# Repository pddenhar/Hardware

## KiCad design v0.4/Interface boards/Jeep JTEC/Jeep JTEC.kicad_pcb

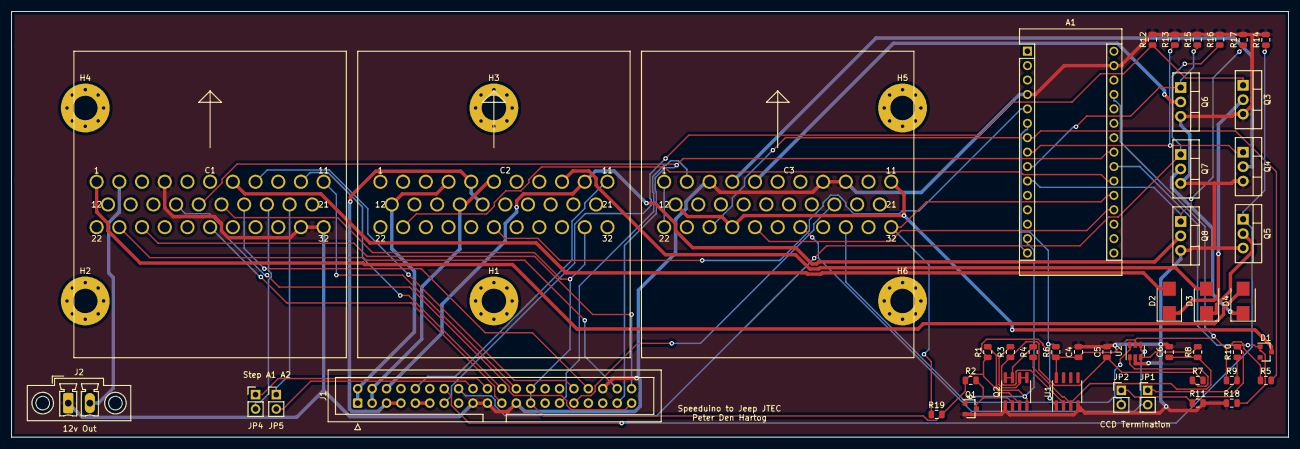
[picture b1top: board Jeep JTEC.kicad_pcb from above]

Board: 2 copper layers, 225.0 x 75.0 mm, 52 parts (0 on the bottom side), 59 nets.

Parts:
A1: Arduino_Nano_v3.x; Arduino_Nano
C1, C2, C3: Conn_01x32; mopar_32pin_pcm
C4: 0.1u; C_0805_2012Metric
C5, C6: 3.3n; C_0805_2012Metric
D1: 10V; SOT-23
D2, D3, D4: D_Schottky 200v; D_SMB
H1, H2, H3, H4, H5, H6: MountingHole; MountingHole_4.3mm_M4_Pad_Via
J1: Conn_02x20_Counter_Clockwise; IDC-Header_2x20_P2.54mm_Vertical
J2: 12v SW Output; PhoenixContact_MCV_1,5_2-GF-3.81_1x02_P3.81mm_Vertical_Thre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
JP1, JP2, JP4, JP5: NO; PinHeader_1x02_P2.54mm_Vertical
Q1: AO3400; SOT-23
Q2: IRF7317; SOIC-8_3.9x4.9mm_P1.27mm
Q3, Q4, Q5, Q6, Q7, Q8: IRF540NPBF; TO-220-3_Vertical
R1, R2, R5, R6, R12, R13, R14, R15, R16, R17, R18, R19: 10k; R_0805_2012Metric
R3, R4: 360; R_0805_2012Metric
R7, R8: 10; R_0805_2012Metric
R9, R11: 13k; R_0805_2012Metric
R10: 120; R_0805_2012Metric
U1: LM2903; SOIC-8_3.9x4.9mm_P1.27mm
U2: USBLC6-2SC6; SOT-23-6

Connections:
12V-SW: C1.2, J2.2
/CCD Decoder/CCD_RX: A1.6, A1.15, R6.2, U1.1
/CCD Decoder/CCD_SAFE+: C5.1, R3.1, R7.2, U1.2
/CCD Decoder/CCD_SAFE-: C6.1, R4.1, R8.1, U1.3
/CCD Decoder/CCD_TX: A1.14, Q1.1, Q2.4, R1.2
/CCD Decoder/NOT-gate: Q1.3, Q2.2, R2.2
AC_CLUTCH_OUT: C3.1, C3.22
ASD_12V_IN: C3.11, C3.12, C3.25, D1.3
ASD_COIL_OUT: A1.4, A1.29, C1.4, C1.31, C1.32, C3.3, C3.8, C3.9, C4.2, C5.2, C6.2, J1.17, J1.19, J1.23, J1.36, J2.1, Q1.2, Q2.1, Q3.3, Q4.3, Q5.3, Q6.3, Q7.3, Q8.3, R11.2, R12.2, R13.2, R14.2, R15.2, R16.2, R17.2, R18.1, U1.4, U2.2
BRAKE_LAMP_SWITCH: A1.7, C3.24, R5.2
CAM-IN: C1.18, J1.34
CCD+: C3.30, JP2.2, U2.6
CCD-: C3.28, JP1.2, U2.4
CLT_Sensor: A1.23, C1.16, J1.37
CRANK-IN: C1.8, J1.32
CRUISE_VAC_CONTROL: A1.8, Q4.1, R13.1
CRUISE_VAC_OUT: C3.4, Q4.2
CRUISE_VENT_CONTROL: A1.9, Q6.1, R15.1
CRUISE_VENT_OUT: C3.5, Q6.2
FAN-OUT: C3.2, J1.29
FUELPUMP-OUT: C3.19, J1.31
FUEL_LEVEL: A1.19, C3.26
GENERATOR_CONTROL: A1.10, Q8.1, R17.1
GENERATOR_GND: C2.10, J1.6, Q8.2
HC-1-OUT: C2.11, J1.10
IAT_Sensor: C1.15, J1.39
IGN-1-DRIVER: C1.7, D2.2
IGN-1-OUT: J1.13, Q3.1, R12.1
IGN-2-DRIVER: C2.9, D3.2
IGN-2-OUT: J1.14, Q5.1, R14.1
IGN-3-DRIVER: C1.1, D4.2
IGN-3-OUT: J1.16, Q7.1, R16.1
INJ-1-OUT: C2.4, C2.12, J1.1, J1.2
INJ-2-OUT: C2.6, C2.15, J1.3, J1.4
INJ-3-OUT: C2.5, C2.16, J1.5, J1.7
INJ-4-OUT: J1.9, J1.11
MAP-EXT: C1.27, J1.21
unnamed: A1.22, D1.1, R18.2
unnamed: C1.19, JP4.2
unnamed: C1.20, JP5.1
unnamed: D2.1, Q3.2
unnamed: D3.1, Q5.2
unnamed: D4.1, Q7.2
unnamed: JP1.1, R9.2, R10.1
unnamed: JP2.1, R10.2, R11.1
unnamed: Q2.5, Q2.6, R3.2
unnamed: Q2.7, Q2.8, R4.2
unnamed: R7.1, U2.1
unnamed: R8.2, U2.3
O2-1-1: C1.24, J1.40
OIL_PRESSURE_IN: A1.21, C2.23
SPEED_CONTROL_SWITCH: A1.20, C3.32, R19.1
STEP-A1: J1.20, JP4.1
STEP-A2: J1.18, JP5.2
STEP-B1: C1.10, J1.22
STEP-B2: C1.11, J1.24
TPS_Sensor: C1.23, J1.38
VDDA: A1.27, C1.17, C2.31, C4.1, J1.25, J1.26, Q2.3, R1.1, R2.1, R5.1, R6.1, R9.1, R19.2, U1.8, U2.5
VSS: A1.5, C2.27

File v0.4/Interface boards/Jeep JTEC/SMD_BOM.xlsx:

Reference(s) | Value | Footprint | Manufacturer | Manufacturer#
C4 | 0.1u | Capacitor_SMD:C_0805_2012Metric | Kemet | C0805C104K5RACTU
C5, C6 | 3.3n | Capacitor_SMD:C_0805_2012Metric | TDK | C2012C0G1H332J060AA
D1 | 10V | Package_TO_SOT_SMD:SOT-23 | BZX84-C10,215 | Nexperia USA Inc.
Q1 | AO3400 | Package_TO_SOT_SMD:SOT-23 | Alpha & Omega Semiconductor Inc. | AO3400A
Q2 | IRF7317 | Package_SO:SOIC-8_3.9x4.9mm_P1.27mm | Infineon | IRF7317TRPBF
R1, R2, R6, R12, R13, R14, R15, R16, R17 | 10k | Resistor_SMD:R_0805_2012Metric | Yageo | RC0805FR-0710KL
R3, R4 | 360 | Resistor_SMD:R_0805_2012Metric | Yageo | RC0805JR-07360RL
R5, R18, R19 | 10k | Resistor_SMD:R_0805_2012Metric | Yageo | RC0805FR-0710KL
R7, R8 | 10 | Resistor_SMD:R_0805_2012Metric | Yageo | RC0805FR-0710RL
R9, R11 | 13k | Resistor_SMD:R_0805_2012Metric | Panasonic | ERJ-6ENF1302V
R10 | 120 | Resistor_SMD:R_0805_2012Metric | Panasonic | ERJP6WF1200V
U1 | LM2903 | Package_SO:SOIC-8_3.9x4.9mm_P1.27mm | onsemi | LM2903DR2G
U2 | USBLC6-2SC6 | Package_TO_SOT_SMD:SOT-666 | STMicroelectronics | USBLC6-2SC6

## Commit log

2021-09-28 Add draft schemtic for Jeep JTEC breakout
2021-09-29 Add pins for extension hardware
2021-09-30 Start building CCD output stage
2021-10-04 Draw Jeep igniters and cruise control drivers
2021-10-04 Add voltage sense circuit for alternator control
2021-10-04 Route PCB for JTEC breakout
2021-10-04 Add BOM items for jellybean parts
2021-10-06 Add jumper for GND and GNDA. Add 12v-SW output
2021-10-07 Add 12v output to PCB
2021-10-07 Add pull up resistor to cruise control input
2021-10-07 Switch project specific symbols to use path substitution
2021-10-08 Add BOM and gerbers
2021-10-09 Correct the footprint for U2
2021-10-09 Correct stepper IAC phases
2021-10-11 Add diodes to igniter circuit to allow ringing
2021-10-21 Correct drill size for JTEC connector
